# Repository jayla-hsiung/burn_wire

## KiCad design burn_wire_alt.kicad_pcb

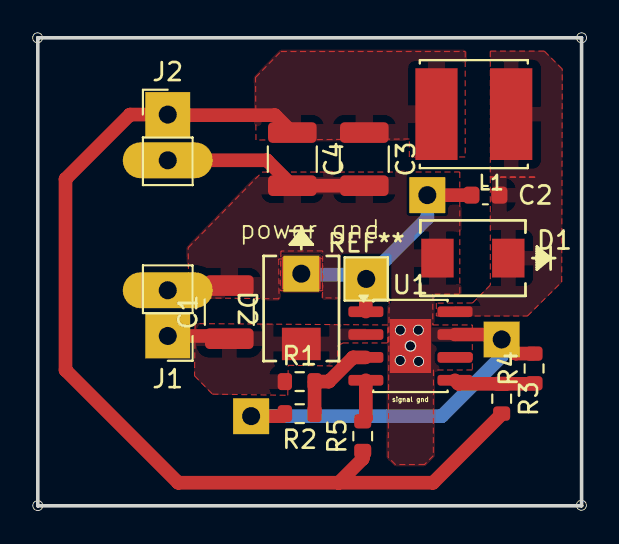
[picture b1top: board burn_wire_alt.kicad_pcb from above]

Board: 2 copper layers, 30.2 x 26.0 mm, 15 parts (0 on the bottom side), 8 nets.

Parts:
C1: 530u; C_1210_3225Metric
C2: 0.1u; C_0603_1608Metric
C3, C4: 47u; C_1210_3225Metric
D1: D_Schottky; CR_SMB_320-345BE_DIO
D2: D_Schottky; CR_SMB_320-345BE_DIO-L
J1, J2: Conn_01x02_Pin; PinHeader_1x02_P2.54mm_Vertical
L1: 3.3u; IND_SRN6045TA-3R3Y
R1: 230k; R_0603_1608Metric
R2, R5: 100k; R_0603_1608Metric
R3, R4: 10k; R_0603_1608Metric
U1: ADP2303ARDZ; SOIC-8-1EP_3.9x4.9mm_P1.27mm_EP2.29x3mm

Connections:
/BST: C2.1, D2.1 (K), U1.1 (BST)
/EN: R1.2, R2.1, U1.3 (EN)
/FB: R3.2, R4.1, U1.5 (FB)
/PGOOD: R5.2, U1.4 (PGOOD)
/SW: C2.2, D1.1 (K), L1.1, U1.8 (SW)
/Vin: C1.1, D2.2 (A), J1.1, R1.1, U1.2 (Vin)
/Vout: C3.1, C4.1, J2.1, L1.2, R3.1, R5.1
GND: C1.2, C3.2, C4.2, D1.2 (A), J1.2, J2.2, R2.2, R4.2, U1.7 (GND), U1.9 (PADGND)

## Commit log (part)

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2026-05-19 initial layout done
2026-05-20 polished layout, agrees with datasheet layout, mostly agrees with buck layout recs article
2026-05-20 forgot to save changes before pushing
2026-05-25 moved fb away from sw
2026-05-25 tweaks
2026-05-25 added bst diode
2026-05-26 rounded corners
2026-05-26 added bst plane under bst diode
2026-06-03 cout connected to agnd
2026-06-03 cout connected to noisy gnd
2026-06-03 board 2 for 6/3
2026-06-04 real values used for board updated schematic
